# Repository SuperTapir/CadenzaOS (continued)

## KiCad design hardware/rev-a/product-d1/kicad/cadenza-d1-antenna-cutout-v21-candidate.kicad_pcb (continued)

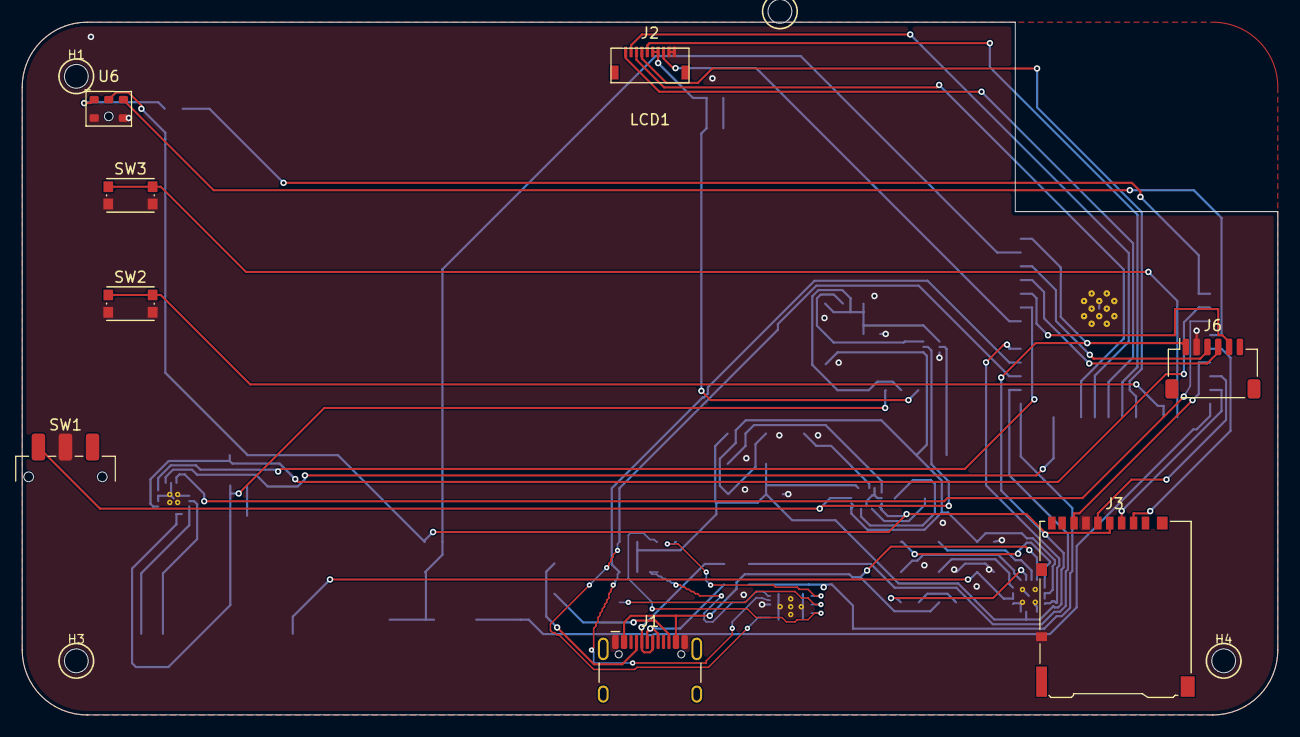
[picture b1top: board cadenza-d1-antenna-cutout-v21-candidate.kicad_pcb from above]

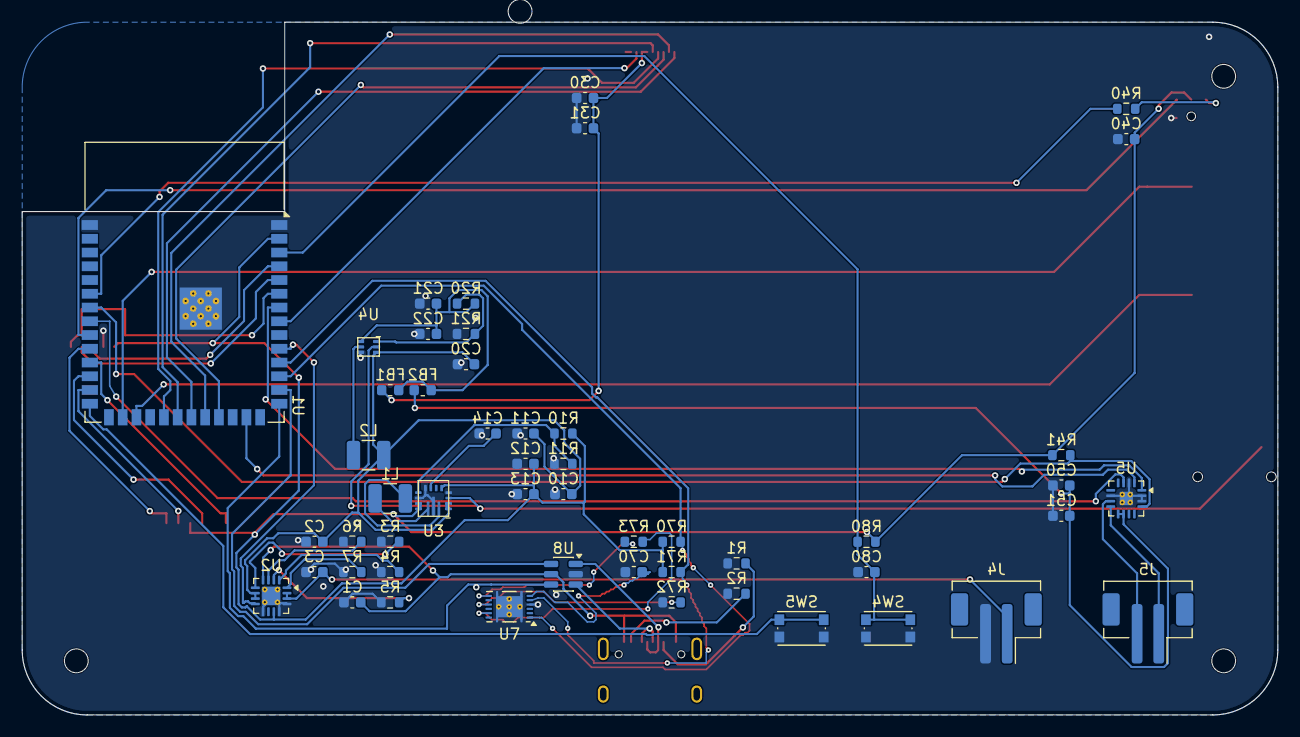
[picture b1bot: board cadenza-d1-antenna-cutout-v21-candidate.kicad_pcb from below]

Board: 4 copper layers, 116.0 x 64.0 mm, 64 parts (51 on the bottom side), 59 nets.

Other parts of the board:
H1: NPTH 2.2mm; H1
H2: NPTH 2.2mm; H2
H3: NPTH 2.2mm; H3
H4: NPTH 2.2mm; H4
LCD1: LS027B7DH01 62.8x42.82; Sharp_LS027B7DH01_Mechanical

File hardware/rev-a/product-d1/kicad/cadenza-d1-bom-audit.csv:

"Refs","Value","Footprint","Qty","DNP"
"C1","10uF","Capacitor_SMD:C_0603_1608Metric","1",""
"C2","10uF","Capacitor_SMD:C_0603_1608Metric","1",""
"C3","10uF","Capacitor_SMD:C_0603_1608Metric","1",""
"C10","10uF","Capacitor_SMD:C_0603_1608Metric","1",""
"C11","10uF","Capacitor_SMD:C_0603_1608Metric","1",""
"C12","22uF","Capacitor_SMD:C_0603_1608Metric","1",""
"C13","22uF","Capacitor_SMD:C_0603_1608Metric","1",""
"C14","100nF","Capacitor_SMD:C_0603_1608Metric","1",""
"C20","10uF","Capacitor_SMD:C_0603_1608Metric","1",""
"C21","22uF","Capacitor_SMD:C_0603_1608Metric","1",""
"C22","22uF","Capacitor_SMD:C_0603_1608Metric","1",""
"C30","1uF","Capacitor_SMD:C_0603_1608Metric","1",""
"C31","100nF","Capacitor_SMD:C_0603_1608Metric","1",""
"C40","100nF","Capacitor_SMD:C_0603_1608Metric","1",""
"C50","10uF","Capacitor_SMD:C_0603_1608Metric","1",""
"C51","100nF","Capacitor_SMD:C_0603_1608Metric","1",""
"C70","1uF","Capacitor_SMD:C_0603_1608Metric","1",""
"C80","1uF","Capacitor_SMD:C_0603_1608Metric","1",""
"FB1","600R@100MHz","Inductor_SMD:L_0603_1608Metric","1",""
"FB2","600R@100MHz","Inductor_SMD:L_0603_1608Metric","1",""
"J1","USB-C USB2 Sink","Connector_USB:USB_C_Receptacle_HCTL_HC-TYPE-C-16P-01A","1",""
"J2","LS027B7DH01 FPC","Cadenza_D1:Hirose_FH34SRJ-10S-0.5SH","1",""
"J3","microSD push-push","Connector_Card:microSD_HC_Hirose_DM3AT-SF-PEJM5","1",""
"J4","LiPo 1S","Connector_JST:JST_PH_B2B-PH-SM4-TB_1x02-1MP_P2.00mm_Vertical","1",""
"J5","Speaker 8R 1-2W","Connector_JST:JST_PH_B2B-PH-SM4-TB_1x02-1MP_P2.00mm_Vertical","1",""
"J6","Encoder daughterboard","Connector_JST:JST_SH_SM06B-SRSS-TB_1x06-1MP_P1.00mm_Horizontal","1",""
"L1","1.2uH Isat>=4.5A","Inductor_SMD:L_1210_3225Metric","1",""
"L2","1uH Isat>=4.5A","Inductor_SMD:L_1210_3225Metric","1",""
"R1","5.1k","Resistor_SMD:R_0603_1608Metric","1",""
"R2","5.1k","Resistor_SMD:R_0603_1608Metric","1",""
"R3","1.5k","Resistor_SMD:R_0603_1608Metric","1",""
"R4","1.18k","Resistor_SMD:R_0603_1608Metric","1",""
"R5","1.5k","Resistor_SMD:R_0603_1608Metric","1",""
"R6","47k","Resistor_SMD:R_0603_1608Metric","1",""
"R7","10k","Resistor_SMD:R_0603_1608Metric","1",""
"R10","470k","Resistor_SMD:R_0603_1608Metric","1",""
"R11","150k","Resistor_SMD:R_0603_1608Metric","1",""
"R20","732k","Resistor_SMD:R_0603_1608Metric","1",""
"R21","100k","Resistor_SMD:R_0603_1608Metric","1",""
"R40","100R","Resistor_SMD:R_0603_1608Metric","1",""
"R41","100k","Resistor_SMD:R_0603_1608Metric","1",""
"R70","4.7k","Resistor_SMD:R_0603_1608Metric","1",""
"R71","4.7k","Resistor_SMD:R_0603_1608Metric","1",""
"R72","10k","Resistor_SMD:R_0603_1608Metric","1",""
"R73","0.01R 1%","Resistor_SMD:R_0603_1608Metric","1",""
"R80","10k","Resistor_SMD:R_0603_1608Metric","1",""
"SW1","POWER RUN/OFF","Button_Switch_SMD:SW_SPDT_CK_JS102011SAQN","1",""
"SW2","B","Button_Switch_SMD:SW_Push_1P1T_NO_CK_KMR2","1",""
"SW3","MENU","Button_Switch_SMD:SW_Push_1P1T_NO_CK_KMR2","1",""
"SW4","RESET","Button_Switch_SMD:SW_Push_1P1T_NO_CK_KMR2","1",""
"SW5","BOOT","Button_Switch_SMD:SW_Push_1P1T_NO_CK_KMR2","1",""
"U1","ESP32-S3-WROOM-1-N16R8","RF_Module:ESP32-S3-WROOM-1","1",""
"U2","BQ24074RGTR","Package_DFN_QFN:VQFN-16-1EP_3x3mm_P0.5mm_EP1.68x1.68mm_ThermalVias","1",""
"U3","TPS63070RNMR","Cadenza_D1:TI_RNM0015A_VQFN-HR-15_TI4222000B","1",""
"U4","TPS61023DRLR","Cadenza_D1:TI_DRL0006A_SOT-563","1",""
"U5","MAX98357AETE+T","Package_DFN_QFN:TQFN-16-1EP_3x3mm_P0.5mm_EP1.23x1.23mm_ThermalVias","1",""
"U6","IM73D122V01","Cadenza_D1:Infineon_IM73D122V01_PG-LLGA-5-3","1",""
"U7","BQ27441DRZR-G1A","Package_SON:Texas_S-PDSO-N12","1",""
"U8","USBLC6-2SC6","Package_TO_SOT_SMD:SOT-23-6","1",""

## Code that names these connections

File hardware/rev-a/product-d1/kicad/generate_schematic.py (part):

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

ESP_PINS = (
    ("GND", "1"), ("3V3", "2"), ("EN", "3"), ("GPIO4", "4"),
    ("GPIO5", "5"), ("GPIO6", "6"), ("GPIO7", "7"), ("GPIO15", "8"),
    ("GPIO16", "9"), ("GPIO17", "10"), ("GPIO18", "11"), ("GPIO8", "12"),
    ("GPIO19", "13"), ("GPIO20", "14"), ("GPIO3", "15"), ("GPIO46", "16"),
    ("GPIO9", "17"), ("GPIO10", "18"), ("GPIO11", "19"), ("GPIO12", "20"),
    ("GPIO13", "21"), ("GPIO14", "22"), ("GPIO21", "23"), ("GPIO47", "24"),
    ("GPIO48", "25"), ("GPIO45", "26"), ("GPIO0", "27"), ("GPIO35", "28"),
    ("GPIO36", "29"), ("GPIO37", "30"), ("GPIO38", "31"), ("GPIO39", "32"),
    ("GPIO40", "33"), ("GPIO41", "34"), ("GPIO42", "35"), ("RXD0", "36"),
    ("TXD0", "37"), ("GPIO2", "38"), ("GPIO1", "39"), ("GND", "40"),
    ("EPAD", "41"),
)
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    Part("U7", "BQ27441DRZR-G1A", "BQ27441", "Package_SON:Texas_S-PDSO-N12", "BQ27441DRZR-G1A", "C473397", 7200, 6200,
         {"1":"I2C_SDA", "2":"I2C_SCL", "3":"GND", "5":"GAUGE_VDD", "6":"PACKP", "7":"VBAT", "8":"PACKP", "10":"GAUGE_BIN", "12":"GAUGE_INT_N", "13":"GND"}),
    Part("J3", "microSD push-push", "MICROSD_10", "Connector_Card:microSD_HC_Hirose_DM3AT-SF-PEJM5", "DM3AT-SF-PEJM5", "C114218", 9700, 6200,
         {"1":"NC", "2":"SD_CS", "3":"SD_CMD", "4":"+3V3_MAIN", "5":"SD_CLK", "6":"GND", "7":"SD_DAT0", "8":"NC", "9":"SD_CD", "10":"GND"}, "Card detect switch to GPIO9; sample-check shell aperture"),
    Part("J6", "Encoder daughterboard", "CONN_6", "Connector_JST:JST_SH_SM06B-SRSS-TB_1x06-1MP_P1.00mm_Horizontal", "SM06B-SRSS-TB", "TBD", 9700, 7600,
         {"1":"+3V3_MAIN", "2":"GND", "3":"ENC_A", "4":"ENC_B", "5":"A_SW", "6":"LED_CTRL"}),
    Part("J4", "LiPo 1S", "CONN_2", "Connector_JST:JST_PH_B2B-PH-SM4-TB_1x02-1MP_P2.00mm_Vertical", "B2B-PH-SM4-TB", "TBD", 4700, 7600, {"1":"PACKP", "2":"GND"}),
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
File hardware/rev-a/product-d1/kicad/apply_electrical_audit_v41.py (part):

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    "/BAT_TS",
})

# ESP32-S3: move product signals away from strapping GPIO45/GPIO46.
set_pad("U1", 9, "/I2S_BCLK")      # GPIO16
set_pad("U1", 16, None)             # GPIO46 strap remains unused
set_pad("U1", 17, "/SD_CD")        # GPIO9
set_pad("U1", 23, "/GAUGE_INT_N")  # GPIO21
set_pad("U1", 26, None)             # GPIO45 strap remains unused
set_pad("U1", 38, "/LED_CTRL")     # GPIO2
set_pad("U1", 39, "/PGOOD_N")      # GPIO1

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clone_footprint("C70", "C71", "1uF", 122.5, 108.0, rotation=180)
assign_two_pin("C71", "/GAUGE_VDD", "/GND")
fp("R72").SetPosition(pos(132.0, 108.0))
assign_two_pin("R72", "/GAUGE_BIN", "/GND")
clone_footprint("R72", "R74", "10k", 136.0, 108.0)
assign_two_pin("R74", "/GAUGE_INT_N", "/+3V3_MAIN")

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clone_footprint("R72", "R76", "100k", 138.0, 87.5)
assign_two_pin("R76", "/PG_3V3_N", "/+3V3_MAIN")
clone_footprint("R72", "R77", "100k", 145.0, 107.0)
assign_two_pin("R77", "/CHG_N", "/+3V3_MAIN")
clone_footprint("R72", "R30", "100k", 124.0, 91.5)
assign_two_pin("R30", "/RUN_EN", "/VSYS")

# microSD pull-ups and local supply bypass.
for ref, signal, x in [
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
